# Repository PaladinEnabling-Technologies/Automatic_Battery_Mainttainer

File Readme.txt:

This is a backup battery charger that I've developed from another design. I've refined it a bit and published the notes on it on my website. Feel free to go read up about it over there:

www.paladintech.wordpress.com

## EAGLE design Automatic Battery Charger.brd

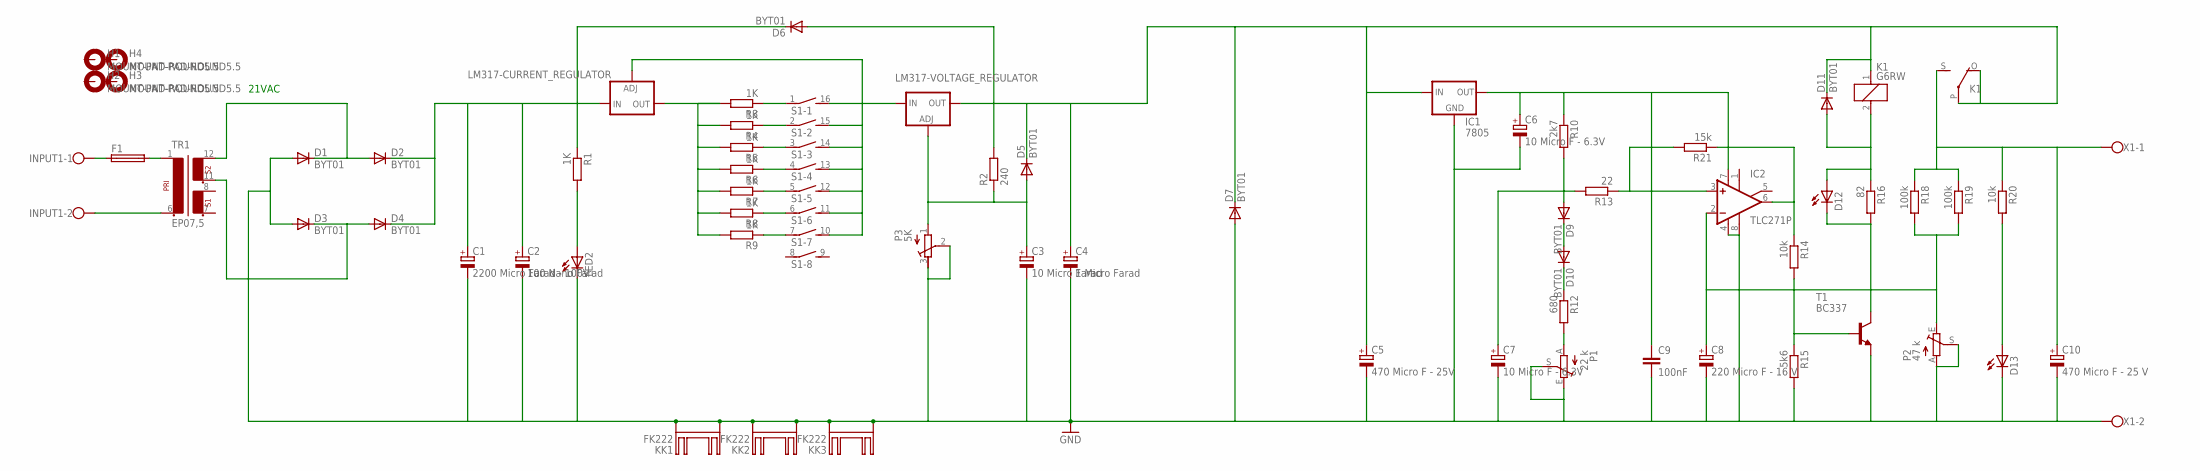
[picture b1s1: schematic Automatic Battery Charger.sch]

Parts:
C1: 2200 Micro Farad - 100V; EB35D
C2: 100 Nano Farad; E1,8-4
C3: 10 Micro Farad; E2-5
C4: 1 Micro Farad; E2-5
C5: 470 Micro F - 25V; E3,5-10
C6, C7: 10 Micro F - 6.3V; E2-5
C8: 220 Micro F - 16 V; E2,5-7
C9: 100nF; C025-030X050
C10: 470 Micro F - 25 V; E3,5-10
D1, D2, D3, D4, D5, D6, D7, D9, D10, D11: BYT01; F126-10
D12, D13: LED5MM
F1: SH22,5A
H1, H2, H3, H4: MOUNT-PAD-ROUND5.5; 5,5-PAD
IC1: 7805; 78XXS
IC2: TLC271P; DIL08
INPUT1: W237-102
K1: G6RW
KK1, KK2, KK3: FK222
LED2: LED5MM
LM317-CURRENT_REGULATOR, LM317-VOLTAGE_REGULATOR: LM138-TS; TO220S
P1: 22 k; LI10
P2: 47 k; LI10
P3: 5K; RTRIM64X
R1, R3, R4, R5: 1K; 0207/7
R2: 240; 0207/7
R6, R7: 1K; 0207/10
R8, R9: 1K; 0207/15
R10: 2k7; 0207/7
R12: 680; 0207/7
R13: 22; 0207/7
R14, R20: 10k; 0207/7
R15: 5k6; 0207/7
R16: 82; 0207/7
R18, R19: 100k; 0207/7
R21: 15k; 0207/7
S1: DIP08SB
T1: BC337; TO92
TR1: EP07,5
X1: W237-102

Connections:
GND: C1.-, C2.-, C3.-, C4.-, C5.-, C6.-, C7.-, C8.-, C9.2, C10.-, D1.A, D3.A, D7.A, D13.K (C), IC1.GND, IC2.4 (V-), IC2.8 (OPT), KK1.A2,8, KK1.B2,8, KK2.A2,8, KK2.B2,8, KK3.A2,8, KK3.B2,8, LED2.K (C), P1.E, P1.S, P2.A, P2.S, P3.2 (S), P3.3 (A), R15.2, T1.1 (E), X1.2
unnamed: C3.+, D5.A, LM317-VOLTAGE_REGULATOR.1 (ADJ), P3.1 (E), R2.1
unnamed: D1.C, D2.A, TR1.12 (6)
unnamed: D3.C, D4.A, TR1.11 (5)
unnamed: R3.1, S1.1
unnamed: R4.1, S1.2 (1)
unnamed: R5.1, S1.3 (1)
unnamed: INPUT1.2, TR1.6 (2)
unnamed: LED2.A, R1.2
unnamed: R6.1, S1.4 (1)
unnamed: F1.2, TR1.1
unnamed: R7.1, S1.5 (1)
unnamed: R8.1, S1.6 (1)
unnamed: R9.1, S1.7 (1)
unnamed: C4.+, C5.+, D5.C, D6.A, D7.C, D11.C, IC1.IN, K1.1, K1.O, K1.P, LM317-VOLTAGE_REGULATOR.2 (OUT), R2.2
unnamed: LM317-CURRENT_REGULATOR.2 (OUT), R3.2, R4.2, R5.2, R6.2, R7.2, R8.2, R9.2
unnamed: F1.1, INPUT1.1
unnamed: LM317-CURRENT_REGULATOR.1 (ADJ), LM317-VOLTAGE_REGULATOR.3 (IN), S1.10 (2), S1.11 (2), S1.12 (2), S1.13 (2), S1.14 (2), S1.15 (2), S1.16 (2)
unnamed: C6.+, C9.1, IC1.OUT, IC2.7 (V+), R10.1
unnamed: C7.+, D9.A, R10.2, R13.2
unnamed: D9.C, D10.A
unnamed: D10.C, R12.1
unnamed: P1.A, R12.2
unnamed: C1.+, C2.+, D2.C, D4.C, D6.C, LM317-CURRENT_REGULATOR.3 (IN), R1.1
unnamed: IC2.3 (+IN), R13.1, R21.2
unnamed: IC2.6 (OUT), R14.1, R21.1
unnamed: R14.2, R15.1, T1.2 (B)
unnamed: D12.K (C), R16.2, T1.3 (C)
unnamed: D11.A, D12.A, K1.2, R16.1
unnamed: C10.+, K1.S, R18.1, R19.1, R20.1, X1.1
unnamed: C8.+, IC2.2 (-IN), P2.E, R18.2, R19.2
unnamed: D13.A, R20.2

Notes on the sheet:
21VAC

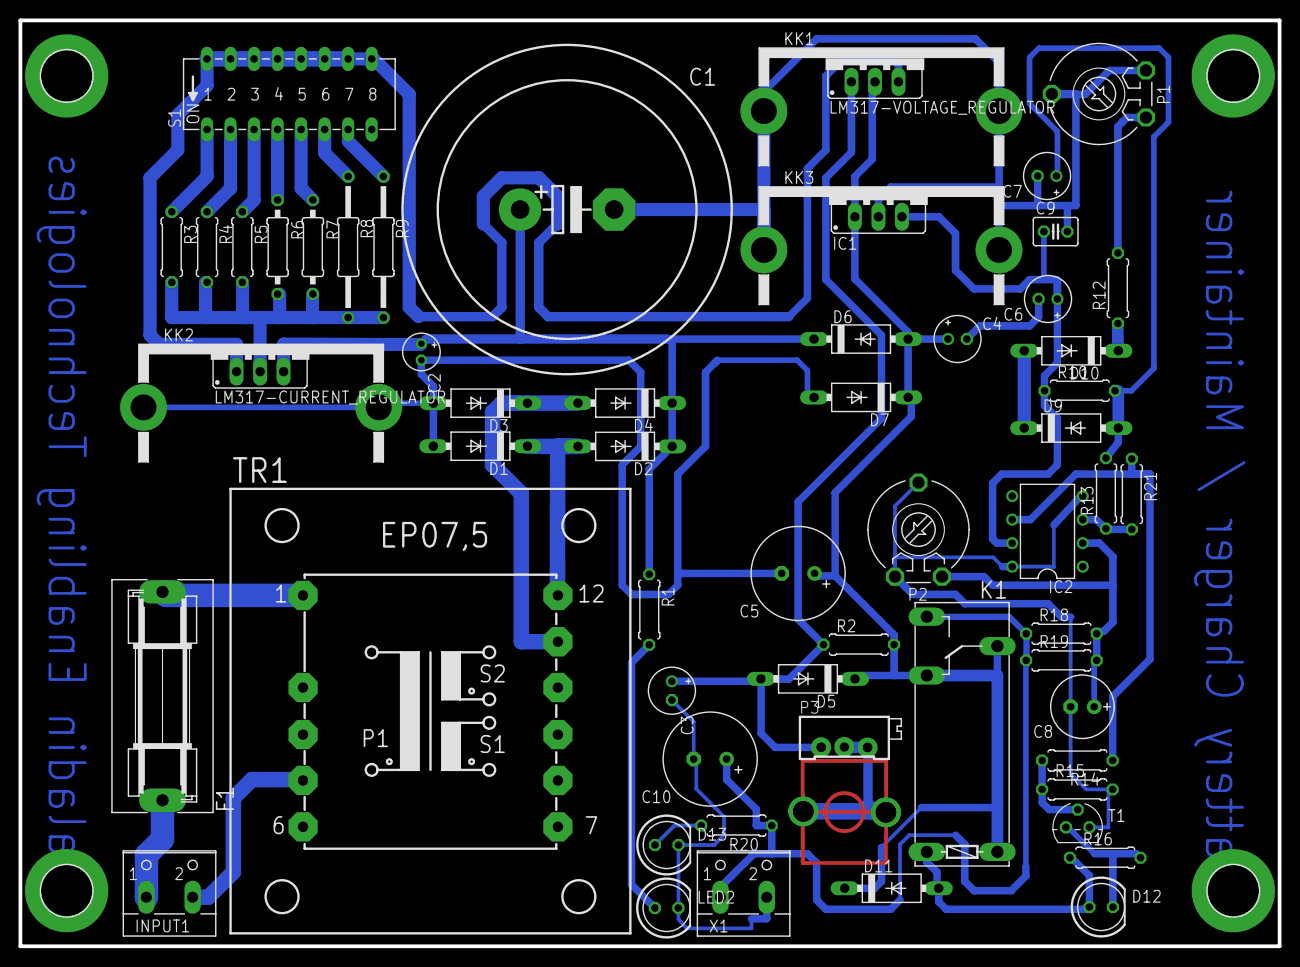
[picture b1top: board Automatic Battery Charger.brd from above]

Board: 2 copper layers, 136.0 x 100.0 mm, 63 parts (0 on the bottom side), 32 nets.

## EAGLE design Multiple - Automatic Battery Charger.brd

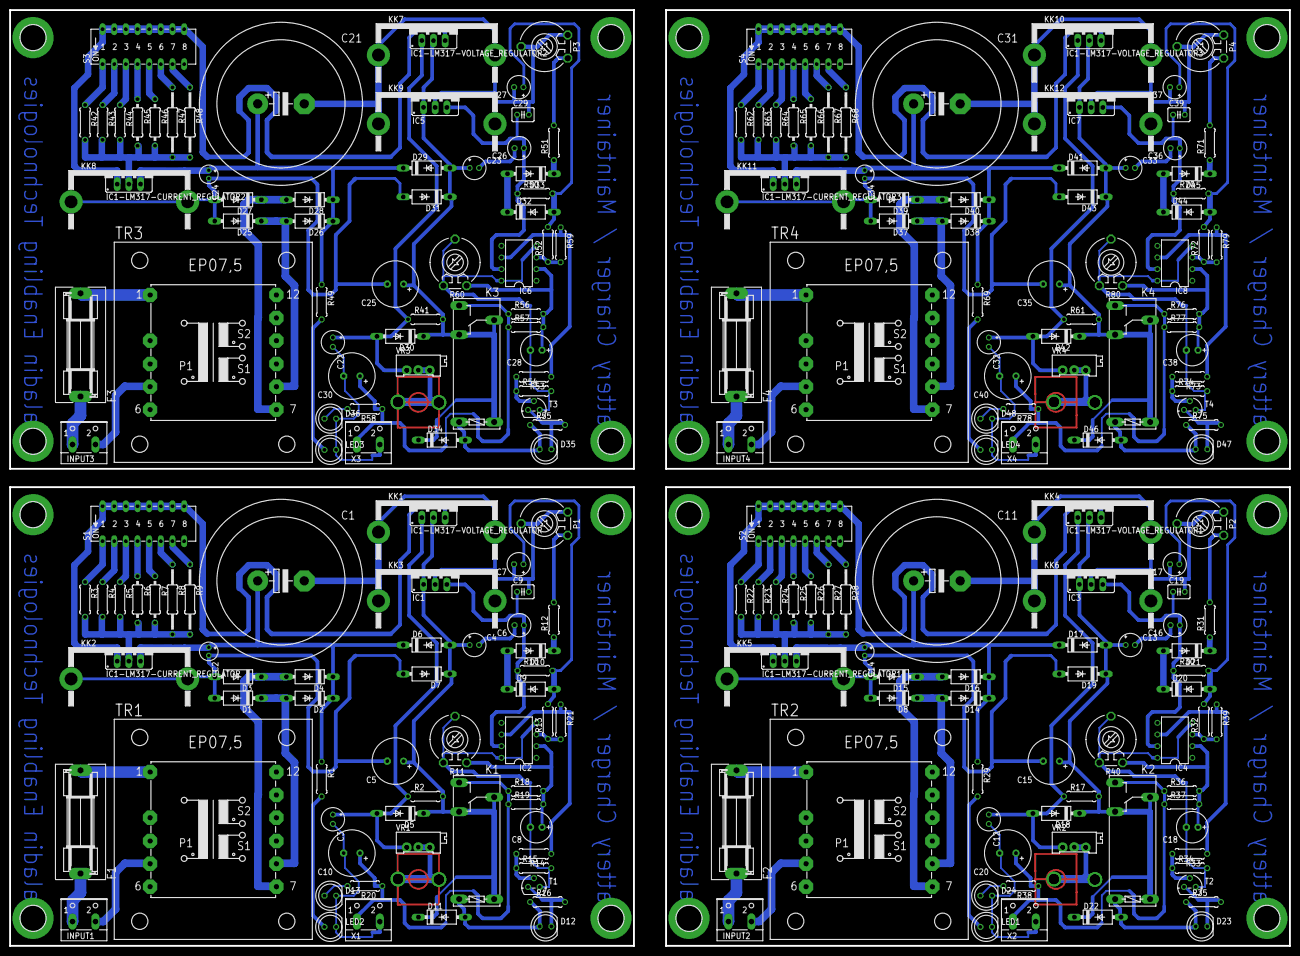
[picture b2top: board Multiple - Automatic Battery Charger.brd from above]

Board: 2 copper layers, 279.0 x 204.0 mm, 252 parts (0 on the bottom side), 128 nets.

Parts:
C1, C11, C21, C31: 2200 Micro Farad - 100V; EB35D
C2, C14, C24, C34: 100 Nano Farad; E1,8-4
C3, C12, C22, C32: 10 Micro Farad; E2-5
C4, C13, C23, C33: 1 Micro Farad; E2-5
C5, C15, C25, C35: 470 Micro F - 25V; E3,5-10
C6, C7, C16, C17, C26, C27, C36, C37: 10 Micro F - 6.3V; E2-5
C8, C18, C28, C38: 220 Micro F - 16 V; E2,5-7
C9, C19, C29, C39: 100nF; C025-030X050
C10, C20, C30, C40: 470 Micro F - 25 V; E3,5-10
D1, D2, D3, D4, D5, D6, D7, D8, D9, D10, D11, D14, D15, D16, D17, D18, D19, D20, D21, D22, D25, D26, D27, D28, D29, D30, D31, D32, D33, D34, D37, D38, D39, D40, D41, D42, D43, D44, D45, D46: BYT01; F126-10
D12, D13, D23, D24, D35, D36, D47, D48: LED5MM
F1, F2, F3, F4: SH22,5A
H1, H2, H3, H4, H5, H6, H7, H8, H9, H10, H11, H12, H13, H14, H15, H16: MOUNT-PAD-ROUND5.5; 5,5-PAD
IC1, IC3, IC5, IC7: 7805; 78XXS
IC1-LM317-CURRENT_REGULATOR, IC1-LM317-CURRENT_REGULATOR1, IC1-LM317-CURRENT_REGULATOR2, IC1-LM317-CURRENT_REGULATOR3, IC1-LM317-VOLTAGE_REGULATOR, IC1-LM317-VOLTAGE_REGULATOR1, IC1-LM317-VOLTAGE_REGULATOR2, IC1-LM317-VOLTAGE_REGULATOR3: TO220S
IC2, IC4, IC6, IC8: TLC271P; DIL08
INPUT1, INPUT2, INPUT3, INPUT4: W237-102
K1, K2, K3, K4: G6RW
KK1, KK2, KK3, KK4, KK5, KK6, KK7, KK8, KK9, KK10, KK11, KK12: FK222
LED1, LED2, LED3, LED4: LED5MM
P1, P2, P3, P4: 22 k; LI10
R1, R3, R4, R5, R22, R23, R24, R29, R42, R43, R44, R49, R62, R63, R64, R69: 1K; 0207/7
R2, R17, R41, R61: 240; 0207/7
R6, R7, R25, R26, R45, R46, R65, R66: 1K; 0207/10
R8, R9, R27, R28, R47, R48, R67, R68: 1K; 0207/15
R10, R30, R50, R70: 2k7; 0207/7
R11, R40, R60, R80: 47 k; LI10
R12, R31, R51, R71: 680; 0207/7
R13, R32, R52, R72: 22; 0207/7
R14, R20, R33, R38, R53, R58, R73, R78: 10k; 0207/7
R15, R34, R54, R74: 5k6; 0207/7
R16, R35, R55, R75: 82; 0207/7
R18, R19, R36, R37, R56, R57, R76, R77: 100k; 0207/7
R21, R39, R59, R79: 15k; 0207/7
S1, S2, S3, S4: DIP08SB
T1, T2, T3, T4: BC337; TO92
TR1, TR2, TR3, TR4: EP07,5
VR1, VR2, VR3, VR4: 5K; RTRIM64X
X1, X2, X3, X4: W237-102

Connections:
GND: C1.-, C2.-, C3.-, C4.-, C5.-, C6.-, C7.-, C8.-, C9.2, C10.-, D1.A, D3.A, D7.A, D13.K, IC1.GND, IC2.4, IC2.8, KK1.A2,8, KK1.B2,8, KK2.A2,8, KK2.B2,8, KK3.A2,8, KK3.B2,8, LED2.K, P1.E, P1.S, R11.A, R11.S, R15.2, T1.1, VR1.2, VR1.3, X1.2
GND1: C11.-, C12.-, C13.-, C14.-, C15.-, C16.-, C17.-, C18.-, C19.2, C20.-, D8.A, D15.A, D19.A, D24.K, IC3.GND, IC4.4, IC4.8, KK4.A2,8, KK4.B2,8, KK5.A2,8, KK5.B2,8, KK6.A2,8, KK6.B2,8, LED1.K, P2.E, P2.S, R34.2, R40.A, R40.S, T2.1, VR2.2, VR2.3, X2.2
GND2: C21.-, C22.-, C23.-, C24.-, C25.-, C26.-, C27.-, C28.-, C29.2, C30.-, D25.A, D27.A, D31.A, D36.K, IC5.GND, IC6.4, IC6.8, KK7.A2,8, KK7.B2,8, KK8.A2,8, KK8.B2,8, KK9.A2,8, KK9.B2,8, LED3.K, P3.E, P3.S, R54.2, R60.A, R60.S, T3.1, VR3.2, VR3.3, X3.2
GND3: C31.-, C32.-, C33.-, C34.-, C35.-, C36.-, C37.-, C38.-, C39.2, C40.-, D37.A, D39.A, D43.A, D48.K, IC7.GND, IC8.4, IC8.8, KK10.A2,8, KK10.B2,8, KK11.A2,8, KK11.B2,8, KK12.A2,8, KK12.B2,8, LED4.K, P4.E, P4.S, R74.2, R80.A, R80.S, T4.1, VR4.2, VR4.3, X4.2
unnamed: C3.+, D5.A, IC1-LM317-VOLTAGE_REGULATOR.1, R2.1, VR1.1
unnamed: D1.C, D2.A, TR1.12
unnamed: D3.C, D4.A, TR1.11
unnamed: R3.1, S1.1
unnamed: R4.1, S1.2
unnamed: R5.1, S1.3
unnamed: INPUT1.2, TR1.6
unnamed: LED2.A, R1.2
unnamed: R6.1, S1.4
unnamed: F1.2, TR1.1
unnamed: R7.1, S1.5
unnamed: R8.1, S1.6
unnamed: R9.1, S1.7
unnamed: C4.+, C5.+, D5.C, D6.A, D7.C, D11.C, IC1.IN, IC1-LM317-VOLTAGE_REGULATOR.2, K1.1, K1.O, K1.P, R2.2
unnamed: IC1-LM317-CURRENT_REGULATOR.2, R3.2, R4.2, R5.2, R6.2, R7.2, R8.2, R9.2
unnamed: F1.1, INPUT1.1
unnamed: IC1-LM317-CURRENT_REGULATOR.1, IC1-LM317-VOLTAGE_REGULATOR.3, S1.10, S1.11, S1.12, S1.13, S1.14, S1.15, S1.16
unnamed: C6.+, C9.1, IC1.OUT, IC2.7, R10.1
unnamed: C7.+, D9.A, R10.2, R13.2
unnamed: D9.C, D10.A
unnamed: D10.C, R12.1
unnamed: P1.A, R12.2
unnamed: C1.+, C2.+, D2.C, D4.C, D6.C, IC1-LM317-CURRENT_REGULATOR.3, R1.1
unnamed: IC2.3, R13.1, R21.2
unnamed: IC2.6, R14.1, R21.1
unnamed: R14.2, R15.1, T1.2
unnamed: D12.K, R16.2, T1.3
unnamed: D11.A, D12.A, K1.2, R16.1
unnamed: C10.+, K1.S, R18.1, R19.1, R20.1, X1.1
unnamed: C8.+, IC2.2, R11.E, R18.2, R19.2
unnamed: D13.A, R20.2
unnamed: D8.C, D14.A, TR2.12
unnamed: D15.C, D16.A, TR2.11
unnamed: C12.+, D18.A, IC1-LM317-VOLTAGE_REGULATOR1.1, R17.1, VR2.1
unnamed: C11.+, C14.+, D14.C, D16.C, D17.C, IC1-LM317-CURRENT_REGULATOR1.3, R29.1
unnamed: INPUT2.2, TR2.6
unnamed: F2.2, TR2.1
unnamed: F2.1, INPUT2.1
unnamed: R22.1, S2.1
unnamed: R23.1, S2.2
unnamed: R24.1, S2.3
unnamed: R25.1, S2.4
unnamed: R26.1, S2.5
unnamed: R27.1, S2.6
unnamed: R28.1, S2.7
unnamed: IC1-LM317-CURRENT_REGULATOR1.2, R22.2, R23.2, R24.2, R25.2, R26.2, R27.2, R28.2
unnamed: IC1-LM317-CURRENT_REGULATOR1.1, IC1-LM317-VOLTAGE_REGULATOR1.3, S2.10, S2.11, S2.12, S2.13, S2.14, S2.15, S2.16
unnamed: LED1.A, R29.2
unnamed: C16.+, C19.1, IC3.OUT, IC4.7, R30.1
unnamed: C17.+, D20.A, R30.2, R32.2
unnamed: D20.C, D21.A
unnamed: D21.C, R31.1
unnamed: P2.A, R31.2
unnamed: IC4.3, R32.1, R39.2
unnamed: IC4.6, R33.1, R39.1
unnamed: R33.2, R34.1, T2.2
unnamed: D23.K, R35.2, T2.3
unnamed: D22.A, D23.A, K2.2, R35.1
unnamed: C20.+, K2.S, R36.1, R37.1, R38.1, X2.1
unnamed: C18.+, IC4.2, R36.2, R37.2, R40.E
unnamed: D24.A, R38.2
unnamed: C13.+, C15.+, D17.A, D18.C, D19.C, D22.C, IC1-LM317-VOLTAGE_REGULATOR1.2, IC3.IN, K2.1, K2.O, K2.P, R17.2
unnamed: D25.C, D26.A, TR3.12
unnamed: D27.C, D28.A, TR3.11
unnamed: C22.+, D30.A, IC1-LM317-VOLTAGE_REGULATOR2.1, R41.1, VR3.1
unnamed: C21.+, C24.+, D26.C, D28.C, D29.C, IC1-LM317-CURRENT_REGULATOR2.3, R49.1
unnamed: INPUT3.2, TR3.6
unnamed: F3.2, TR3.1
unnamed: F3.1, INPUT3.1
unnamed: R42.1, S3.1
unnamed: R43.1, S3.2
unnamed: R44.1, S3.3
unnamed: R45.1, S3.4
unnamed: R46.1, S3.5
unnamed: R47.1, S3.6
unnamed: R48.1, S3.7
unnamed: IC1-LM317-CURRENT_REGULATOR2.2, R42.2, R43.2, R44.2, R45.2, R46.2, R47.2, R48.2
unnamed: IC1-LM317-CURRENT_REGULATOR2.1, IC1-LM317-VOLTAGE_REGULATOR2.3, S3.10, S3.11, S3.12, S3.13, S3.14, S3.15, S3.16
unnamed: LED3.A, R49.2
unnamed: C26.+, C29.1, IC5.OUT, IC6.7, R50.1
unnamed: C27.+, D32.A, R50.2, R52.2
unnamed: D32.C, D33.A
unnamed: D33.C, R51.1
unnamed: P3.A, R51.2
unnamed: IC6.3, R52.1, R59.2
unnamed: IC6.6, R53.1, R59.1
unnamed: R53.2, R54.1, T3.2
unnamed: D35.K, R55.2, T3.3
unnamed: D34.A, D35.A, K3.2, R55.1
unnamed: C30.+, K3.S, R56.1, R57.1, R58.1, X3.1
unnamed: C28.+, IC6.2, R56.2, R57.2, R60.E
unnamed: D36.A, R58.2
unnamed: C23.+, C25.+, D29.A, D30.C, D31.C, D34.C, IC1-LM317-VOLTAGE_REGULATOR2.2, IC5.IN, K3.1, K3.O, K3.P, R41.2
unnamed: D37.C, D38.A, TR4.12
unnamed: D39.C, D40.A, TR4.11
unnamed: C32.+, D42.A, IC1-LM317-VOLTAGE_REGULATOR3.1, R61.1, VR4.1
unnamed: C31.+, C34.+, D38.C, D40.C, D41.C, IC1-LM317-CURRENT_REGULATOR3.3, R69.1
unnamed: INPUT4.2, TR4.6
unnamed: F4.2, TR4.1
unnamed: F4.1, INPUT4.1
unnamed: R62.1, S4.1
unnamed: R63.1, S4.2
unnamed: R64.1, S4.3
unnamed: R65.1, S4.4
unnamed: R66.1, S4.5
unnamed: R67.1, S4.6
unnamed: R68.1, S4.7
unnamed: IC1-LM317-CURRENT_REGULATOR3.2, R62.2, R63.2, R64.2, R65.2, R66.2, R67.2, R68.2
unnamed: IC1-LM317-CURRENT_REGULATOR3.1, IC1-LM317-VOLTAGE_REGULATOR3.3, S4.10, S4.11, S4.12, S4.13, S4.14, S4.15, S4.16
unnamed: LED4.A, R69.2
unnamed: C36.+, C39.1, IC7.OUT, IC8.7, R70.1
unnamed: C37.+, D44.A, R70.2, R72.2
unnamed: D44.C, D45.A
unnamed: D45.C, R71.1
unnamed: P4.A, R71.2
unnamed: IC8.3, R72.1, R79.2
unnamed: IC8.6, R73.1, R79.1
unnamed: R73.2, R74.1, T4.2
unnamed: D47.K, R75.2, T4.3
unnamed: D46.A, D47.A, K4.2, R75.1
unnamed: C40.+, K4.S, R76.1, R77.1, R78.1, X4.1
unnamed: C38.+, IC8.2, R76.2, R77.2, R80.E
unnamed: D48.A, R78.2
unnamed: C33.+, C35.+, D41.A, D42.C, D43.C, D46.C, IC1-LM317-VOLTAGE_REGULATOR3.2, IC7.IN, K4.1, K4.O, K4.P, R61.2

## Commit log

2014-03-08 Added some additional files
    more files
